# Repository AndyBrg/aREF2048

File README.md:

# aREF2048
Precision Voltage Reference 2.048V

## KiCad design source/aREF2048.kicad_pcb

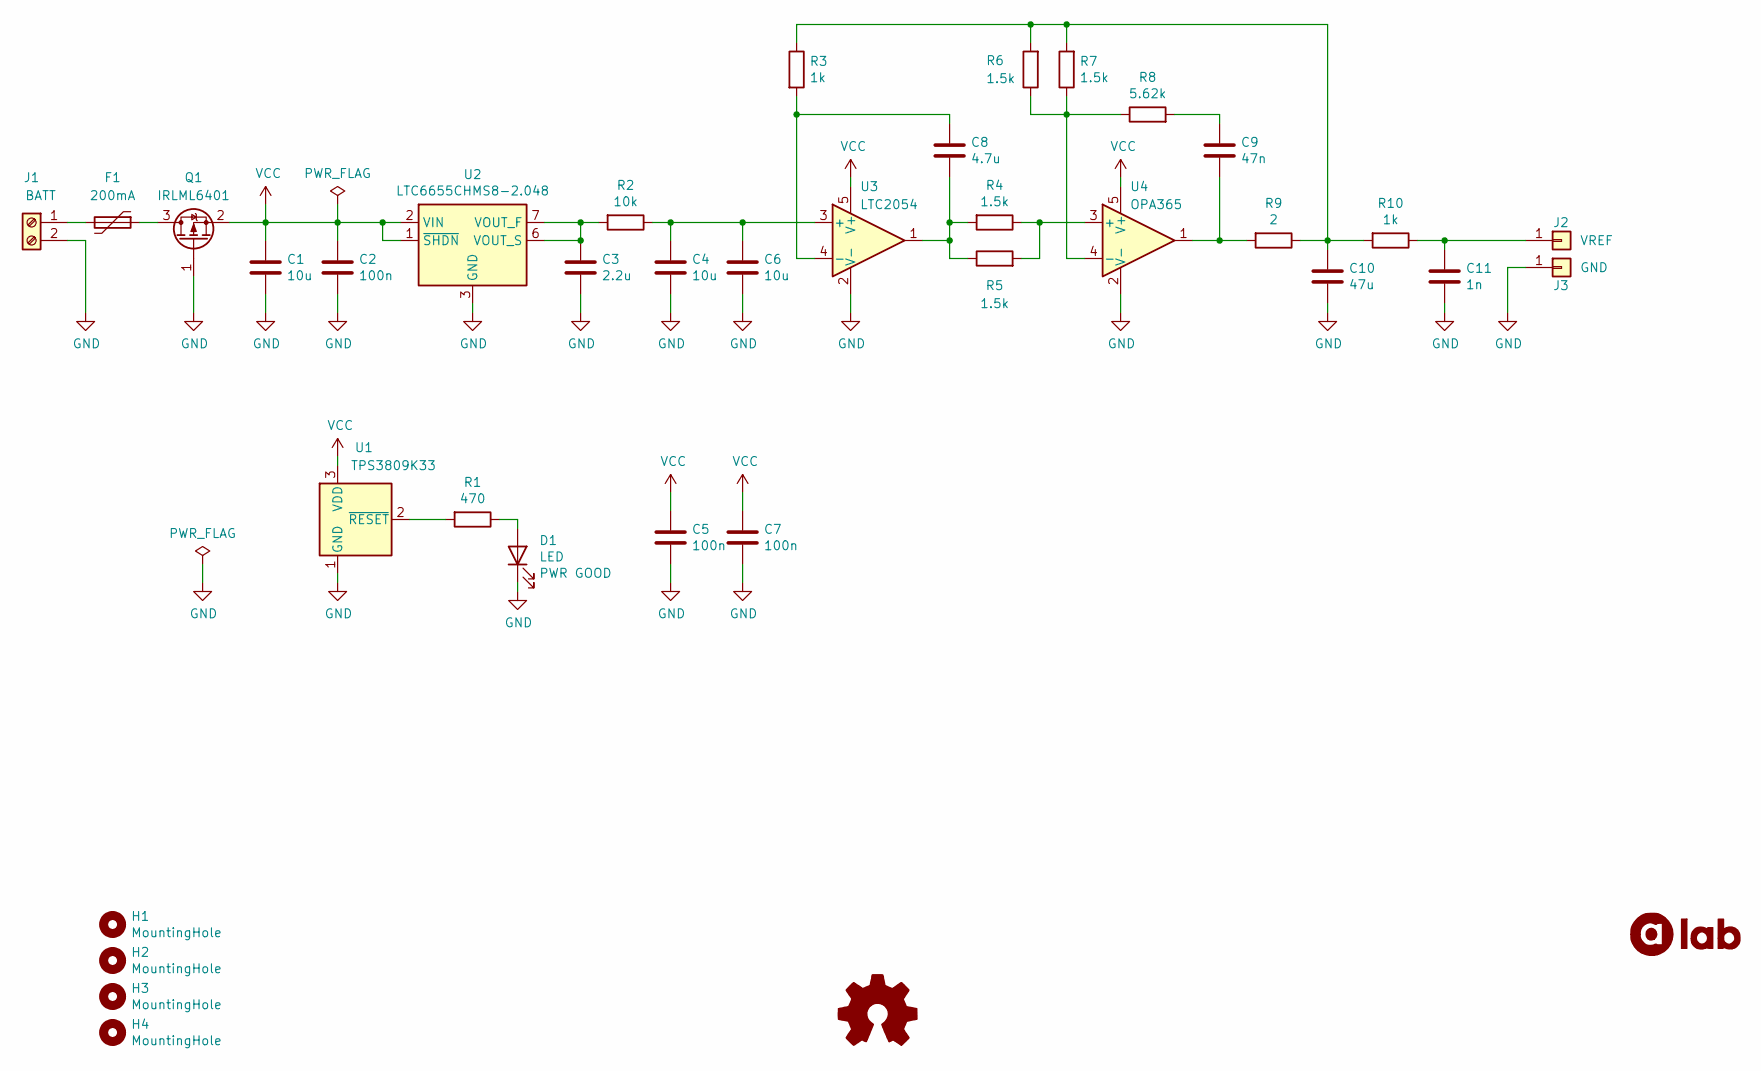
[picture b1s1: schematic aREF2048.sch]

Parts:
C1: 10u; C_0603_1608Metric_Pad1.08x0.95mm_HandSolder; Part Number GRM188R61C106KAALD
C2, C5, C7: 100n; C_0603_1608Metric_Pad1.08x0.95mm_HandSolder; Part Number CC0603JRX7R9BB104
C3: 2.2u; C_0603_1608Metric_Pad1.08x0.95mm_HandSolder; Part Number GRM188R61E225MA12D
C4, C6: 10u; C_Rect_L18.5mm_W8.5mm_P15.00mm_FKS3_FKP3; Part Number MKT1820610065
C8: 4.7u; C_0603_1608Metric_Pad1.08x0.95mm_HandSolder; Part Number GRM188R61A475KE15D
C9: 47n; C_0603_1608Metric_Pad1.08x0.95mm_HandSolder; Part Number CL10B473KB8NNNC
C10: 47u; C_1210_3225Metric_Pad1.33x2.70mm_HandSolder; Part Number GRM32ER71A476KE15L
C11: 1n; C_0603_1608Metric_Pad1.08x0.95mm_HandSolder; Part Number CC0603JRNPO8BN102
D1: LED; LED_D3.0mm; Part Number L-1154GT
F1: 200mA; Fuse_0805_2012Metric_Pad1.15x1.40mm_HandSolder; Part Number MF-PSMF020X-2
H1, H2, H3, H4: MountingHole; MountingHole_2.2mm_M2
J1: BATT; TerminalBlock_Phoenix_PT-1,5-2-3.5-H_1x02_P3.50mm_Horizontal; Part Number DG350-3.5-02P-14-00AH
J2: VREF; Pin_D1.0mm_L10.0mm_LooseFit
J3: GND; Pin_D1.0mm_L10.0mm_LooseFit
Q1: IRLML6401; SOT-23
R1: 470; R_0603_1608Metric_Pad0.98x0.95mm_HandSolder; Part Number RC0603FR-07470RL
R2: 10k; R_0805_2012Metric_Pad1.20x1.40mm_HandSolder; Part Number RT0805BRD0710KL
R3, R10: 1k; R_0805_2012Metric_Pad1.20x1.40mm_HandSolder; Part Number RT0805BRD071KL
R4, R5, R6, R7: 1.5k; R_0805_2012Metric_Pad1.20x1.40mm_HandSolder; Part Number RT0805BRD071K5L
R8: 5.62k; R_0805_2012Metric_Pad1.20x1.40mm_HandSolder; Part Number RT0805BRD075K62L
R9: 2; R_0805_2012Metric_Pad1.20x1.40mm_HandSolder; Part Number RT0805BRD072RL
U1: TPS3809K33; SOT-23; Part Number TPS3809K33DBVR
U2: LTC6655CHMS8-2.048; MSOP-8_3x3mm_P0.65mm
U3: LTC2054; SOT-23-5; Part Number LTC2054IS5#PBF
U4: OPA365; SOT-23-5; Part Number OPA365AIDBVT

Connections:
GND: C1.2, C2.2, C3.2, C4.2, C5.2, C6.2, C7.2, C10.2, C11.2, D1.1 (K), J1.2, J3.1, Q1.1 (G), U1.1 (GND), U2.3 (GND), U2.4 (GND), U2.5 (GND), U2.8 (GND), U3.2 (V-), U4.2 (V-)
unnamed: C3.1, R2.2, U2.6 (VOUT_S), U2.7 (VOUT_F)
unnamed: C4.1, C6.1, R2.1, U3.3 (+)
unnamed: C8.1, R3.2, U3.4 (-)
unnamed: C8.2, R4.2, R5.1, U3.1
unnamed: C9.1, R8.2
unnamed: C9.2, R9.2, U4.1
unnamed: C10.1, R3.1, R6.2, R7.2, R9.1, R10.2
unnamed: C11.1, J2.1, R10.1
unnamed: D1.2 (A), R1.1
unnamed: F1.1, Q1.3 (D)
unnamed: F1.2, J1.1
unnamed: R1.2, U1.2 (~RESET)
unnamed: R4.1, R5.2, U4.3 (+)
unnamed: R6.1, R7.1, R8.1, U4.4 (-)
VCC: C1.1, C2.1, C5.1, C7.1, Q1.2 (S), U1.3 (VDD), U2.1 (~SHDN), U2.2 (VIN), U3.5 (V+), U4.5 (V+)

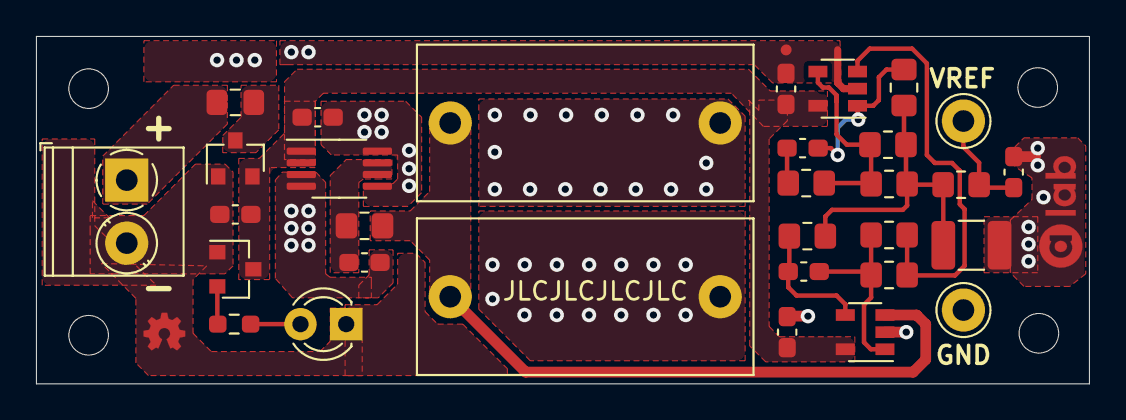
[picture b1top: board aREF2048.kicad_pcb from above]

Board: 2 copper layers, 58.5 x 19.3 mm, 35 parts (0 on the bottom side), 16 nets.

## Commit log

2021-07-27 Add datasheets
2021-07-27 Add project
2021-07-27 Move files
2021-07-29 Version 0.1
2021-09-27 Add circuit pdf
2021-09-27 Add BOM and Title
